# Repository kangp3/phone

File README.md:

# phone

This is a repository containing some code artifacts but mostly testing fragments for a project to develop a device to
connect landline phones to other landline phones via a private VoIP network. At time of writing of this README
(July 2024) efforts are mostly focused on the design of the hardware side of the project, but this repository may
come to house more complete companion software as the project grows.

1. ~~Ring phone via software~~
    - Completed in [ring.py](ring.py)
2. ~~Play audio on phone speaker~~
    - Completed in [wav.py](wav.py)
3. ~~Receive audio from phone and convert to digital signal~~
4. Parse DTMF signals for dialing
5. Create system for initial phone setup
6. Create web app for call routing and social networking

## Development Utilities

### SSH
The Pi is set up with the hostname `peterpi.local` and can be SSH'ed to using the username `recurse`.
```
ssh recurse@peterpi.local
```

### SSH setup
```
sudo sed --in-place=.bak --expression='s/^#PermitEmptyPasswords no/PermitEmptyPasswords yes/g' /etc/ssh/sshd_config
sudo systemctl restart sshd
sudo passwd -d recurse
```

### Dial tone generator
These commands are used to send sine wave signals to the speakers of the Pi. By correctly routing the
output audio device of the Pi to "headphones" routed to pins, these signals can be sent to the phone.
The following two sine waves are the frequencies used in a standard dial tone.
```
speaker-test -t sine -f 350 -l0
speaker-test -t sine -f 440 -l0
```

### Cross-compile to Rasppi (old stinky cross-rs way)
```
cross build --target=arm-unknown-linux-gnueabihf
```

### Device Tree compile
```
scp phoneodeo.dts recurse@peterpi.local:
scp bootconfig.txt recurse@peterpi.local:
```
```
dtc -@ -H epapr -O dtb -o phoneodeo.dtbo -Wno-unit_address_vs_reg phoneodeo.dts
sudo cp phoneodeo.dtbo /boot/overlays
sudo chown root:root bootconfig.txt
sudo chmod 755 bootconfig.txt
sudo cp bootconfig.txt /boot/firmware/config.txt
```

### Install phreak.service
```
scp goertzel/phreak.service recurse@peterpi.local:
scp goertzel/phreak.timer recurse@peterpi.local:
scp goertzel/target/arm-unknown-linux-gnueabihf/release/goertzel recurse@peterpi.local:
```
```
sudo chown root:root ~/phreak.service
sudo chmod 777 ~/phreak.service
sudo mv ~/phreak.service /etc/systemd/system
sudo systemctl disable phreak.service
sudo systemctl enable phreak.service

sudo chown root:root ~/phreak.timer
sudo chmod 777 ~/phreak.timer
sudo mv ~/phreak.timer /etc/systemd/system
sudo systemctl enable phreak.timer
sudo systemctl start phreak.timer
```

### Install .asoundrc
```
scp asoundrc recurse@peterpi.local:.asoundrc
```
```
sudo cp .asoundrc /root
```

### Set volume
```
amixer sset PCM -M '40%'
sudo alsactl store
```

### Take down Wi-Fi
```
sudo nmcli connection delete 'Recurse Center'; sudo reboot
```

### Cross-compile
Install some cross-compilation dependencies
```
brew tap messense/macos-cross-toolchains
brew install arm-unknown-linux-gnueabihf
rustup target add arm-unknown-linux-gnueabihf
brew install cmake  # dependency of aws-lc-sys
cargo install --force --locked bindgen-cli  # dependency of aws-lc-sys
```
Need to pass the sysroot in order to get around this error:
```
  --- stderr
  /Users/peter/.cargo/registry/src/index.crates.io-1949cf8c6b5b557f/aws-lc-sys-0.30.0/aws-lc/include/openssl/base.h:61:10: fatal error: 'stdlib.h' file not found

  thread 'main' panicked at /Users/peter/.cargo/registry/src/index.crates.io-1949cf8c6b5b557f/aws-lc-sys-0.30.0/builder/sys_bindgen.rs:110:10:
  Unable to generate bindings.: ClangDiagnostic("/Users/peter/.cargo/registry/src/index.crates.io-1949cf8c6b5b557f/aws-lc-sys-0.30.0/aws-lc/include/openssl/base.h:61:10: fatal error: 'stdlib.h' file not found\n")
  note: run with `RUST_BACKTRACE=1` environment variable to display a backtrace
```
Got some help from these sources:
- https://stackoverflow.com/questions/65392271/macos-big-sur-11-1-cant-find-stdlib-h-w
- https://github.com/rust-lang/rust-bindgen?tab=readme-ov-file#environment-variables
- https://aws.github.io/aws-lc-rs/requirements/linux.html#linux-requirements
- https://github.com/apache/opendal/pull/5004/files
```
BINDGEN_EXTRA_CLANG_ARGS=--sysroot="$(xcrun --sdk macosx --show-sdk-path)" cargo build --release --target=arm-unknown-linux-gnueabihf
```

### Cross-compile dialbutton
Install some cross-compilation dependencies
```
brew tap messense/macos-cross-toolchains
brew install x86_64-unknown-linux-gnu
export CARGO_TARGET_X86_64_UNKNOWN_LINUX_GNU_LINKER=x86_64-linux-gnu-gcc
```
Helpful resources:
- https://github.com/messense/homebrew-macos-cross-toolchains
```
PATH="$PATH:/opt/homebrew/Cellar/x86_64-unknown-linux-gnu/13.3.0/bin" cargo build --release --target x86_64-unknown-linux-gnu --features http --bin dialbutton
```

### PBX
```
wget https://downloads.asterisk.org/pub/telephony/asterisk/asterisk-20-current.tar.gz
tar -xzvf asterisk-20-current.tar.gz
cd asterisk-20.9.3
./contrib/scripts/install_prereq install &&
./configure &&
make &&
make install
```

### Update users
Edit pjsip.conf on the remote
```
asterisk -x 'module reload'
```

### Certbot
```
sudo apt-get update
sudo apt-get install -y snapd
sudo snap install --classic certbot
sudo ln -s /snap/bin/certbot /usr/bin/certbot
sudo certbot -d pbx.frandline.com --manual --preferred-challenges dns certonly --manual-auth-hook /home/ubuntu/renew.sh
sudo su
```
```
curl -LsSf https://astral.sh/uv/install.sh | sh
```

Test:
```
sudo certbot renew --dry-run
```

### socat wiring on Windows
Cygwin:
```
socat -t30 -T30 UDP4-RECVFROM:5060,fork UDP4:"$(wsl hostname -I | tr -d ' ')":5062 &
socat -t30 -T30 UDP4-RECVFROM:5061,fork UDP4:"$(wsl hostname -I | tr -d ' ')":5063 &
```

### ssh wiring on Windows:
PowerShell (administrator):
```
netsh interface portproxy add v4tov4 listenaddress=x.x.x.x listenport=22 connectaddress=$($(wsl hostname -I).Trim()) connectport=22
netsh advfirewall firewall add rule name=”Open Port 22 for WSL2” dir=in action=allow protocol=TCP localport=22
```

## Helpful links
- [Security Group](https://us-east-2.console.aws.amazon.com/ec2/home?region=us-east-2#SecurityGroup:group-id=sg-04dbcc9ef474c2027)
- [Docker Asterisk](https://github.com/mlan/docker-asterisk)
- [Phil's SSL Guide](https://www.phildev.net/ssl/)
- [Certbot Asterisk](https://feeding.cloud.geek.nz/posts/using-letsencrypt-cert-with-asterisk/)

## Relevant Material
- [SLIC datasheet](https://silvertel.com/images/datasheets/Ag1171-datasheet-Low-cost-ringing-SLIC-with-single-supply.pdf)
- [gpiozero docs](https://gpiozero.readthedocs.io/en/latest/)
- [Cringely-named DT overlay](https://github.com/AkiyukiOkayasu/RaspberryPi_I2S_Slave)
    - Comment out playback and codec_out
    - dai-tdm-slot-width to 24
    - Add in capture_link block mclk-fs = <256>
    - Add in r_codec_dai system-clock-frequency = <2560000>

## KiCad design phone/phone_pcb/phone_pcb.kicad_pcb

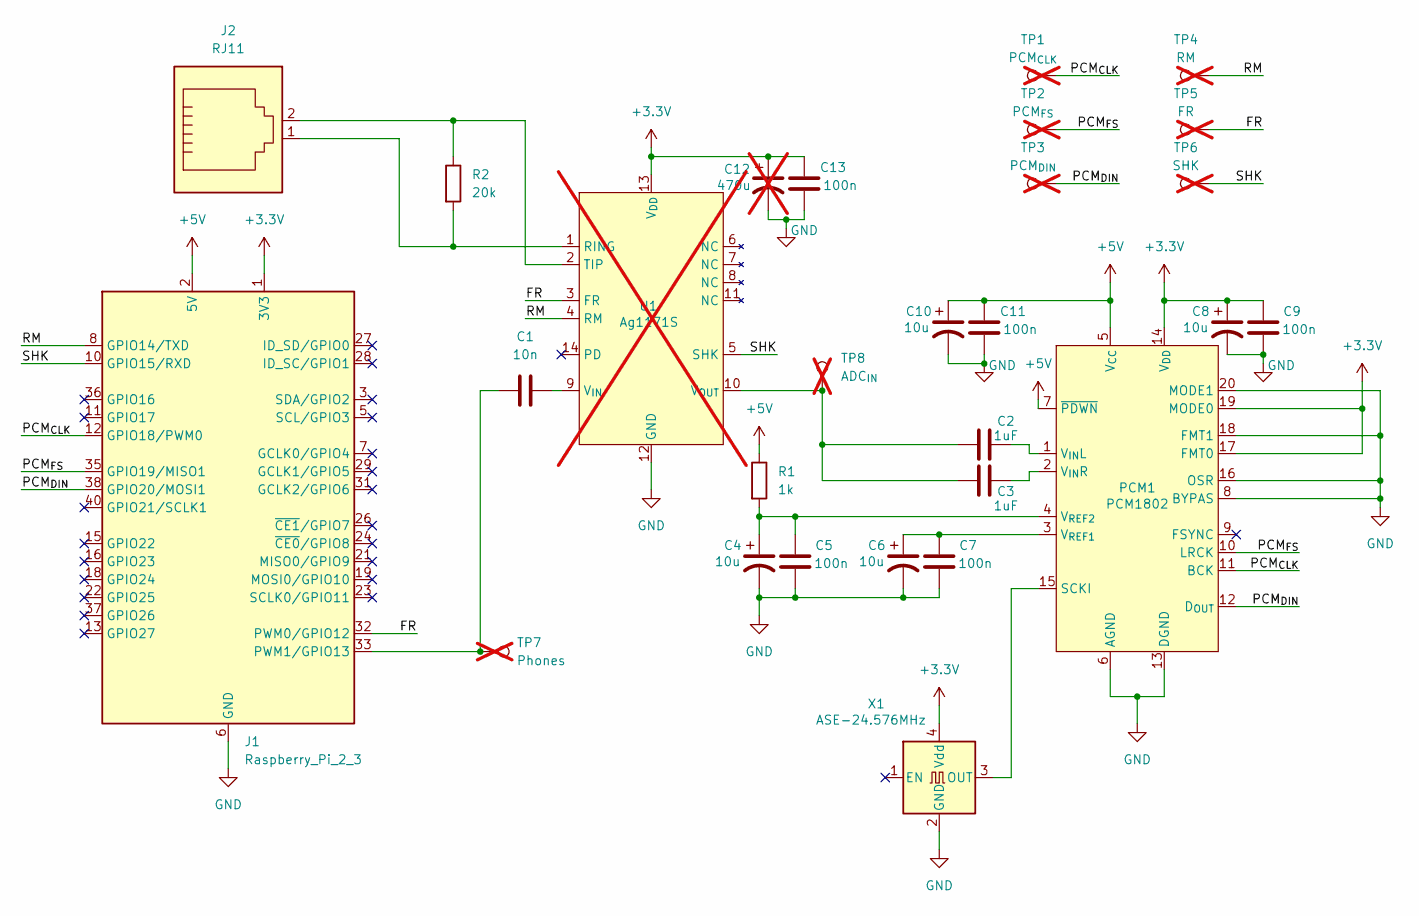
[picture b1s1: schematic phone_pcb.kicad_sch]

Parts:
C1: 10n; C_0402_1005Metric; LCSC C15195
C2, C3: 1uF; C_0402_1005Metric; LCSC C52923
C4, C6, C8, C10: 10u; CP_EIA-3216-18_Kemet-A; LCSC C7171
C5, C7, C9, C11, C13: 100n; C_0402_1005Metric; LCSC C1525
C12: 470u; C_Radial_D6.3mm_H7.0mm_P2.50mm; not fitted
J1: Raspberry_Pi_2_3; PinHeader_2x20_P2.54mm_Vertical; LCSC C25503128
J2: RJ11; RJ11_Ckmtw_A800_Horizontal; LCSC C189748
PCM1: PCM1802; SSOP-20_5.3x7.2mm_P0.65mm; LCSC C2866894
R1: 1k; R_0402_1005Metric; LCSC C11702
R2: 20k; R_0805_2012Metric; LCSC C4328
TP1: PCM_{CLK}; TestPoint_THTPad_D2.0mm_Drill1.0mm; not fitted
TP2: PCM_{FS}; TestPoint_THTPad_D2.0mm_Drill1.0mm; not fitted
TP3: PCM_{DIN}; TestPoint_THTPad_D2.0mm_Drill1.0mm; not fitted
TP4: RM; TestPoint_THTPad_D2.0mm_Drill1.0mm; not fitted
TP5: FR; TestPoint_THTPad_D2.0mm_Drill1.0mm; not fitted
TP6: SHK; TestPoint_THTPad_D2.0mm_Drill1.0mm; not fitted
TP7: Phones; TestPoint_THTPad_D2.0mm_Drill1.0mm; not fitted
TP8: ADC_{IN}; TestPoint_THTPad_D2.0mm_Drill1.0mm; not fitted
U1: Ag1171S; PinHeader_1x7+7_P2.54mm_Vertical; not fitted
X1: ASE-24.576MHz; Oscillator_SMD_Abracon_ASE-4Pin_3.2x2.5mm; LCSC C437128

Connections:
+3.3V: C8.1, C9.2, C12.1, C13.2, J1.1 (3V3), J1.17 (3V3), PCM1.14 (V_{DD}), PCM1.17 (FMT0), PCM1.19 (MODE0), U1.13 (V_{DD}), X1.4 (Vdd)
+5V: C10.1, C11.2, J1.2 (5V), J1.4 (5V), PCM1.5 (V_{CC}), PCM1.7 (~PDWN), R1.1
/FR: J1.32 (PWM0/GPIO12), TP5.1, U1.3 (FR)
/PCM_{CLK}: J1.12 (GPIO18/PWM0), PCM1.11 (BCK), TP1.1
/PCM_{DIN}: J1.38 (GPIO20/MOSI1), PCM1.12 (D_{OUT}), TP3.1
/PCM_{FS}: J1.35 (GPIO19/MISO1), PCM1.10 (LRCK), TP2.1
/RM: J1.8 (GPIO14/TXD), TP4.1, U1.4 (RM)
/SHK: J1.10 (GPIO15/RXD), TP6.1, U1.5 (SHK)
GND: C4.2, C5.1, C6.2, C7.1, C8.2, C9.1, C10.2, C11.1, C12.2, C13.1, J1.6 (GND), J1.9 (GND), J1.14 (GND), J1.20 (GND), J1.25 (GND), J1.30 (GND), J1.34 (GND), J1.39 (GND), PCM1.6 (AGND), PCM1.8 (BYPAS), PCM1.13 (DGND), PCM1.16 (OSR), PCM1.18 (FMT1), PCM1.20 (MODE1), U1.12 (GND), X1.2 (GND); also elsewhere on the board
unnamed: C1.1, J1.33 (PWM1/GPIO13), TP7.1
unnamed: PCM1.15 (SCKI), X1.3 (OUT)
unnamed: C2.2, PCM1.1 (V_{IN}L)
unnamed: C3.2, PCM1.2 (V_{IN}R)
unnamed: C6.1, C7.2, PCM1.3 (V_{REF1})
unnamed: C4.1, C5.2, PCM1.4 (V_{REF2}), R1.2
unnamed: J2.1, R2.2, U1.1 (RING)
unnamed: J2.2, R2.1, U1.2 (TIP)
unnamed: C1.2, U1.9 (V_{IN})
unnamed: C2.1, C3.1, TP8.1, U1.10 (V_{OUT})

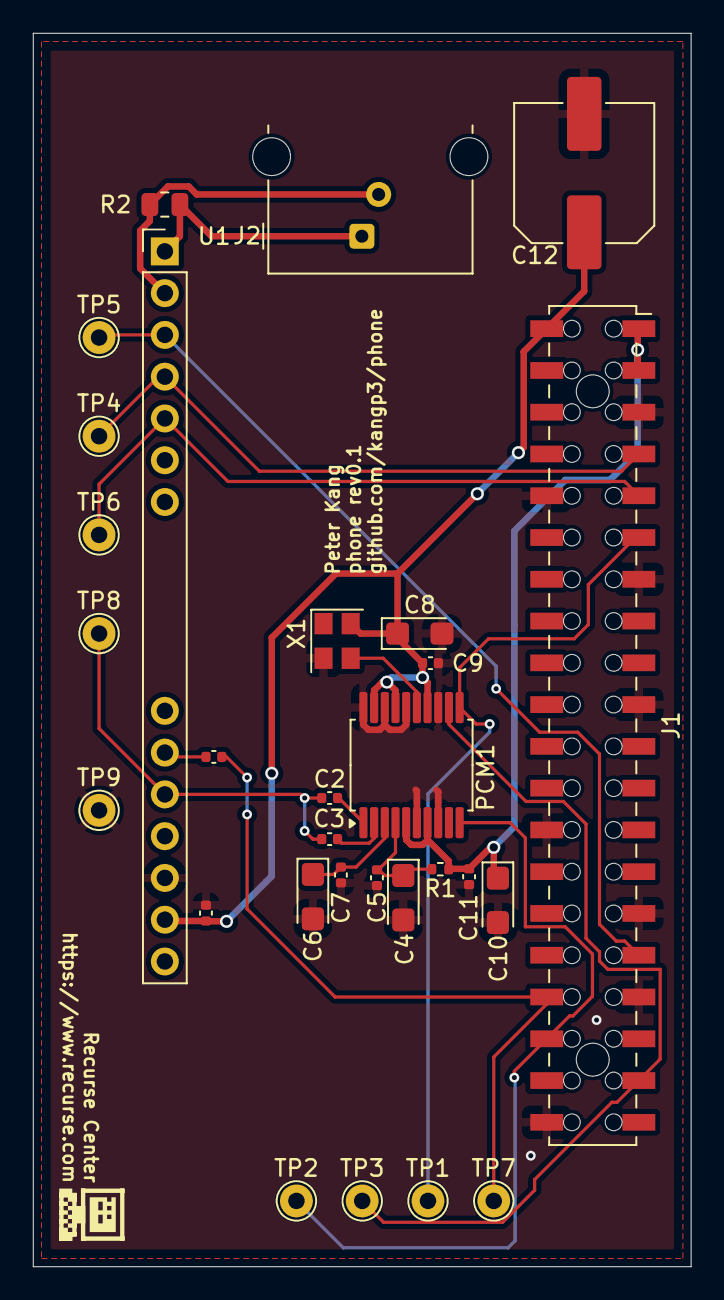
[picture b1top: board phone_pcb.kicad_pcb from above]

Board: 2 copper layers, 40.0 x 75.0 mm, 29 parts (0 on the bottom side), 19 nets.

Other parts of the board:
TP9: GND; TestPoint_THTPad_D2.0mm_Drill1.0mm

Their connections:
GND: TP9.1; also elsewhere on the board

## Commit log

2024-06-15 It ring haha
2024-06-17 Get off-hook detection working
2024-06-17 Make a dial tone
2024-06-17 Try enabling pins
2024-06-17 Dial tone experimentation
2024-06-17 Play dial tone on pickup
2024-06-20 Dial looping
2024-06-20 Simple ringing script
2024-07-10 Some more testing stuff
2024-07-10 Fix up README
2024-07-10 Fix indentation of bullets
2024-07-10 Swap heading styles
2024-07-15 Add working(?) boot config
2024-07-17 Get audio ADC working!!!!!
2024-07-22 Move audio samples to directory
2024-07-22 Logic analyzer output
2024-07-23 DTMF detector
2024-07-23 More audio samples
2024-07-23 Finding ones yayyyyyyy
2024-07-23 Yet more detection of nummers
2024-07-24 Detect digits live
2024-07-24 Use a ring buffer for storing samples
2024-07-24 Only print one digit at a time
2024-07-24 Cross-compilation with a Dockerfile @soenkehahn
2024-07-26 Oh man this encoding is FUCKED UP
2024-07-26 Improve error handling
2024-07-29 Clean original cortelco dial tones
2024-07-30 Use command-line arg for fname
2024-07-30 Simplify match statement
2024-08-02 Add relative magnitude thresholding to Python DTMF
2024-08-02 Grab a more compatible device
2024-08-02 Goertzeler online
2024-08-02 Properly handle when samples is dead
2024-08-03 Remove unused debug log
2024-08-03 Input from mic!!1!
2024-08-03 Use relative thresholding
2024-08-03 Implement Hamming window
2024-08-04 Allow file or mic
2024-08-04 Compare against background avg not just next value
2024-08-04 MULTI-GOERTZELING
2024-08-06 Just some HTML nothin too craaaazy
2024-08-06 Spectrogrammer
2024-08-06 Deploy to GH pages
2024-08-06 Try to fix GH action
2024-08-06 Try updating GH action permissions
2024-08-06 Fuck this peaceiris bullshit and fuck ChatGPT
2024-08-06 IDK try bumping the checkout action version
2024-08-06 Fix the dang old artifact path
2024-08-06 Move mode button to 1
2024-08-06 Also encode password
2024-08-06 Just a little bit of styling
2024-08-06 Do some debugging on the Pi
2024-08-08 Get sound overlay working
2024-08-08 Clean up old device tree stuff
2024-08-08 Clean up
2024-08-08 Everything in f32s
2024-08-08 We have some new goodness for you and it is proper delimiting of repeat numberssssssss
2024-08-08 Add a TODO
2024-08-08 Yay CSS yay yay
2024-08-08 We async'ed I guess
2024-08-08 Tear out file parsing and output
2024-08-10 We async'ed it!
2024-08-10 Remove unused imports
2024-08-10 Break things out into modules
2024-08-10 YAy it read characters
2024-08-12 Make a default for State
2024-08-12 Simplify the translation to chars
2024-08-12 Correctly name the sextile
2024-08-13 Handle the 0 control character correctly
2024-08-13 Consolidate case where different digit pressed
2024-08-14 Set up Wi-Fi!
2024-08-15 Wi-Fi service on startup!
2024-09-02 KiCAD files
2024-09-03 Design the PCB!
2024-09-03 Do some DNPs
2024-09-04 Rev0.1 of PCB :D
2024-09-05 Use local copy of alsa-sys
2024-09-05 Cross-compilation works!
2024-09-06 Some PCB updates
2024-09-06 ctrl-c slammin on macos
2024-09-06 Fix compile on RPi
2024-09-06 Add Wi-Fi connection commands for mac
2024-09-06 Support WAV files again upside-down-smile-emoji
2024-09-09 Add some DTMF audio samples
2024-09-11 WIP got all unwraps out of main
2024-09-11 Error handing to deco::ding
2024-09-11 We got it!!!
2024-09-13 Improve error handling in loops
2024-09-13 Clean up my async error handling!
2024-09-18 Yay it works on WAV files!
2024-09-19 Tune DTMF params
2024-09-19 Set max level to trace in release
2024-09-19 Feature for wifi
2024-09-19 Offload sample scaling to Goertzeler
2024-09-19 Fix bad state management for when to send decoded digits?
2024-09-19 Some more tuning
2024-09-20 Support pulse dialing
2024-09-20 Touch up pulse dialing implementation
2024-09-22 Add PBX installation instructions
2024-09-22 Split up Goertzeler loop into some helpers
2024-09-22 Create binary for testing WAV files
2024-09-23 Correctly calculate total energy
2024-09-23 Fix digit decode handling
2024-09-23 Tune DTMF detection params
2024-09-23 Tuning to remove noisy 1s
2024-09-24 Begin sketching out the state machine :o
2024-09-24 Use match statement for state management
2024-09-24 It rings again!!
2024-09-24 Touch up error states and initialization
2024-09-24 Get Wi-Fi working again!!
2024-09-24 Add helper for creating combined digit channel
2024-09-24 Refactor so we're not goertzeling 24/7
2024-09-25 SIP is registeringggg
2024-09-25 Ring da bell
2024-09-26 Checkpoint
2024-09-26 Ok it's working now to port it to the new
2024-09-26 Touch up the lock management
2024-09-26 Build helper to add auth to a request
2024-09-26 Sprinkle around some SIP registration
2024-09-26 It rings!!!!!!
2024-09-27 Handle CANCEL requests during ringing
2024-09-27 Dialing
2024-09-28 Flesh out README instructions
2024-09-29 Holy moly picking up the phone works
2024-09-29 Handle BYEs correctly
2024-09-30 Some progress but audio loops back to same device?
2024-09-30 it kind of works it's racy though
2024-09-30 Filter out SDP responses outside of network
2024-09-30 Override response address in contact header
2024-09-30 UDP sock read and write in separate tokio tasks
2024-09-30 Refactor to fix port open race
2024-10-01 Clean up teardown of decoding/DTMF tokio tasks
2024-10-01 Adjust dialing timeout and block dialing yourself
2024-10-01 Busy tones work?
2024-10-02 Use i16s for audio
2024-10-07 Adjust params to work in hub
2024-10-15 Create LICENSE
2025-03-04 Update Asterisk TLS config
2025-03-18 TLS install
2025-03-18 WIP tlser binary
2025-03-22 Add link to security group
2025-07-13 Add certbot renewal script
2025-07-20 Touch up certbot renew
2025-08-04 Get auth response from server
2025-08-17 Move certbot to deploy dir
2025-08-17 Script for adding IP to security group
2025-08-18 Clean up existing rules from security group
2025-08-18 Deserialize response
2025-08-20 Get public IP
2025-08-21 Add public IP helper
2025-08-21 Pass IP into SIP Dialog
2025-08-23 Abstract tlssocket behind channels
2025-08-23 Work with SipMessage instead of Request
2025-08-23 Add missing tlssocket file
2025-08-23 Get auth working
2025-08-23 cargo fmt
2025-08-23 Allow passing server host and port to bind
2025-08-23 Create a TLSConn struct
2025-08-23 Move bind() to TLSConn::new()
2025-08-24 Push message passing down to Dialog level
2025-08-24 Use the unwrapped value for Call ID
2025-08-24 Create send/recv helpers
2025-08-24 Add debug logging
2025-08-24 Only debug log first message line
2025-08-24 Tweak debug logging
2025-08-24 Move register into helper method
2025-08-24 Move things around
2025-08-24 Pass username and password into dialog
2025-08-24 Get server host from TLS conn
2025-08-24 Get INVITE sent between clients
2025-08-24 Use a single TLS conn
2025-08-25 Relax Clone impl on Dialog
2025-08-25 Get rid of silly extra msg roundtrip
2025-08-25 Send ringing response
2025-08-25 Fix body handling
2025-08-25 Complete ringing round-trip
2025-08-25 Split into dialed and dialer
2025-08-25 Clean up from/to handling
2025-08-25 Fix phone.rs
2025-08-25 Clean up old files
2025-08-25 Move user/pass loading to main
2025-08-25 Update TODOs
2025-08-25 Some more TODOs
2025-08-25 Migrate error handling to anyhow
2025-08-26 Get cross-compilation working
2025-08-26 Swap around dialer user
2025-08-27 WIP fix dialing
2025-08-27 Set up dialbutton HTTP server
2025-08-27 Return 500 on phone 404
2025-08-27 Add logging
2025-08-28 More logging
2025-08-28 Remove debug logging
2025-08-28 It's a button
2025-08-28 Add some CORS
2025-08-28 POST to dial
2025-08-28 Add a status box
2025-08-28 Get rid of startup ring
2025-08-28 Replace ExecStartPre with a timer
2025-12-03 Start some simple unit tests
2025-12-14 Add a little more to test
2025-12-14 Add Docker container for Asterisk
